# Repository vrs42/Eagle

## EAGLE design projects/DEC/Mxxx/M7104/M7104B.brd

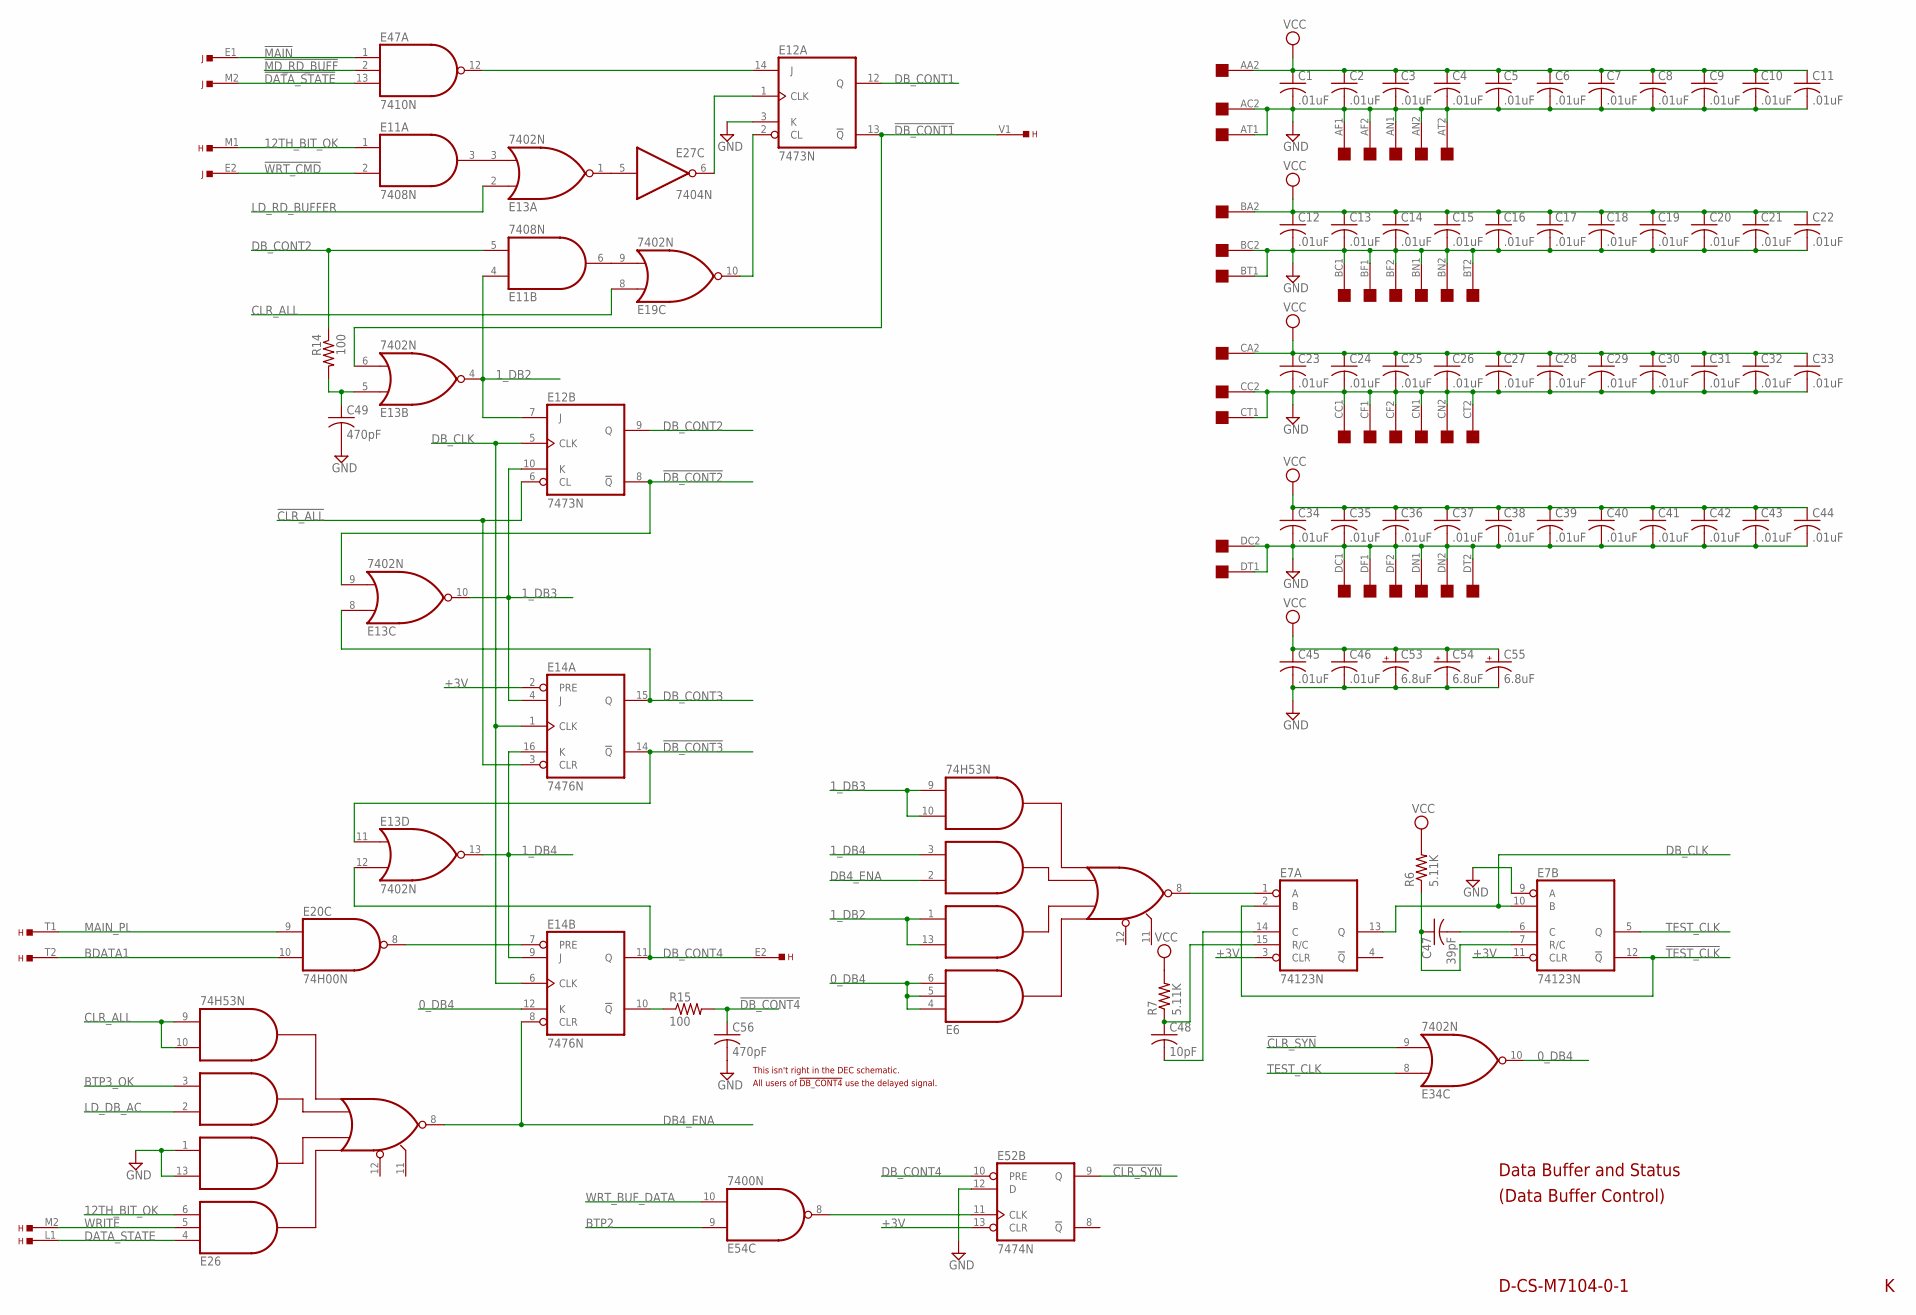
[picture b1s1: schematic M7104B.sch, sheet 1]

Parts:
C1, C2, C3, C4, C5, C6, C7, C8, C9, C10, C11, C12, C13, C14, C15, C16, C17, C18, C19, C20, C21, C22, C23, C24, C25, C26, C27, C28, C29, C30, C31, C32, C33, C34, C35, C36, C37, C38, C39, C40, C41, C42, C43, C44, C45, C46: .01uF; C063-025X075
C47: 39pF; C063-025X075
C48: 10pF; C063-025X075
C49, C56: 470pF; C063-025X075
C53, C54, C55: 6.8uF; E12-8
E6, E26: 74H53N; DIL14
E7: 74123N; DIL16
E11: 7408N; DIL14
E12: 7473N; DIL14
E13, E19, E34: 7402N; DIL14
E14: 7476N; DIL16
E20: 74H00N; DIL14
E27: 7404N; DIL14
E47: 7410N; DIL14
E52: 7474N; DIL14
E54: 7400N; DIL14
H: EDGE-TOP; EDGE-CON2
J: EDGE-TOP; EDGE-CON2
OMNIBUS: QUAD; EDGE-CON8
R6, R7: 5.11K; 0207/15
R14, R15: 100; 0207/10

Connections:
0_DB4: E6.4 (I1), E6.5 (I11), E6.6 (I2), E14.12 (K), E34.10 (O)
1_DB2: E6.1 (I4), E6.13 (I3), E11.4 (I0), E12.7 (J), E13.4 (O)
1_DB3: E6.9 (I8), E6.10 (I7), E12.10 (K), E13.10 (O), E14.4 (J)
1_DB4: E6.3 (I6), E13.13 (O), E14.9 (J), E14.16 (K); also elsewhere on the board
12TH_BIT_OK: E11.1 (I0), E26.6 (I2), H.M1
!CLR_ALL: E12.6 (CL), E14.3 (CLR); also elsewhere on the board
!CLR_SYN: E34.9 (I1), E52.9 (Q)
!DATA_STATE: E47.13 (I2), J.M2
!DB_CONT1: E12.13 (!Q), E13.6 (I1), H.V1
!DB_CONT2: E12.8 (!Q), E13.9 (I1); also elsewhere on the board
!DB_CONT3: E13.11 (I0), E14.14 (!Q)
!DB_CONT4: C56.1, R15.2; also elsewhere on the board
!MAIN: E47.1 (I0), J.E1; also elsewhere on the board
!MD_RD_BUFF: E47.2 (I1); also elsewhere on the board
!TEST_CLK: E7.2 (B), E7.12 (!Q)
!WRT_CMD: E11.2 (I1), J.E2; also elsewhere on the board
+3V: E7.3 (CLR), E7.11 (CLR), E14.2 (PRE), E52.13 (CLR); also elsewhere on the board
BDATA1: E20.10 (I1), H.T2
BTP2: E54.9 (I0); also elsewhere on the board
BTP3_OK: E26.3 (I6); also elsewhere on the board
CLR_ALL: E19.8 (I0), E26.9 (I8), E26.10 (I7); also elsewhere on the board
DATA_STATE: E26.4 (I1), H.L1
DB4_ENA: E6.2 (I5), E14.8 (CLR), E26.8 (O)
DB_CLK: E7.10 (B), E7.13 (Q), E12.5 (CLK), E14.1 (CLK), E14.6 (CLK); also elsewhere on the board
DB_CONT1: E12.12 (Q); also elsewhere on the board
DB_CONT2: E11.5 (I1), E12.9 (Q), R14.1; also elsewhere on the board
DB_CONT3: E13.8 (I0), E14.15 (Q); also elsewhere on the board
DB_CONT4: E13.12 (I1), E14.11 (Q), E52.10 (PRE), H.E2
GND: C1.2, C2.2, C3.2, C4.2, C5.2, C6.2, C7.2, C8.2, C9.2, C10.2, C11.2, C12.2, C13.2, C14.2, C15.2, C16.2, C17.2, C18.2, C19.2, C20.2, C21.2, C22.2, C23.2, C24.2, C25.2, C26.2, C27.2, C28.2, C29.2, C30.2, C31.2, C32.2, C33.2, C34.2, C35.2, C36.2, C37.2, C38.2, C39.2, C40.2, C41.2, C42.2, C43.2, C44.2, C45.2, C46.2, C49.2, C53.-, C54.-, C55.-, C56.2, E6.7 (GND), E7.8 (GND), E7.9 (A), E11.7 (GND), E12.3 (K), E12.11 (GND), E13.7 (GND), E14.13 (GND), E19.7 (GND), E20.7 (GND), E26.1 (I4), E26.7 (GND), E26.13 (I3), E27.7 (GND), E34.7 (GND), E47.7 (GND), E52.7 (GND), E52.12 (D), E54.7 (GND), OMNIBUS.AC2, OMNIBUS.AF1, OMNIBUS.AF2, OMNIBUS.AN1, OMNIBUS.AN2, OMNIBUS.AT1, OMNIBUS.AT2, OMNIBUS.BC1, OMNIBUS.BC2, OMNIBUS.BF1, OMNIBUS.BF2, OMNIBUS.BN1, OMNIBUS.BN2, OMNIBUS.BT1, OMNIBUS.BT2, OMNIBUS.CC1, OMNIBUS.CC2, OMNIBUS.CF1, OMNIBUS.CF2, OMNIBUS.CN1, OMNIBUS.CN2, OMNIBUS.CT1, OMNIBUS.CT2, OMNIBUS.DC1, OMNIBUS.DC2, OMNIBUS.DF1, OMNIBUS.DF2, OMNIBUS.DN1, OMNIBUS.DN2, OMNIBUS.DT1, OMNIBUS.DT2; also elsewhere on the board
LD_DB_AC: E26.2 (I5); also elsewhere on the board
LD_RD_BUFFER: E13.2 (I0); also elsewhere on the board
MAIN_PL: E20.9 (I0), H.T1
unnamed: E14.10 (!Q), R15.1
unnamed: E12.14 (J), E47.12 (O)
unnamed: C48.1, E7.15 (R/C), R7.1
unnamed: E11.3 (O), E13.3 (I1)
unnamed: E13.1 (O), E27.5 (I)
unnamed: E12.1 (CLK), E27.6 (O)
unnamed: E11.6 (O), E19.9 (I1)
unnamed: E12.2 (CL), E19.10 (O)
unnamed: E52.11 (CLK), E54.8 (O)
unnamed: C49.1, E13.5 (I0), R14.2
unnamed: E6.8 (O), E7.1 (A)
unnamed: C47.1, E7.7 (R/C), R6.1
unnamed: C47.2, E7.6 (C)
unnamed: C48.2, E7.14 (C)
unnamed: E14.7 (PRE), E20.8 (O)
TEST_CLK: E7.5 (Q), E34.8 (I0)
VCC: C1.1, C2.1, C3.1, C4.1, C5.1, C6.1, C7.1, C8.1, C9.1, C10.1, C11.1, C12.1, C13.1, C14.1, C15.1, C16.1, C17.1, C18.1, C19.1, C20.1, C21.1, C22.1, C23.1, C24.1, C25.1, C26.1, C27.1, C28.1, C29.1, C30.1, C31.1, C32.1, C33.1, C34.1, C35.1, C36.1, C37.1, C38.1, C39.1, C40.1, C41.1, C42.1, C43.1, C44.1, C45.1, C46.1, C53.+, C54.+, C55.+, E6.14 (VCC), E7.16 (VCC), E11.14 (VCC), E12.4 (VCC), E13.14 (VCC), E14.5 (VCC), E19.14 (VCC), E20.14 (VCC), E26.14 (VCC), E27.14 (VCC), E34.14 (VCC), E47.14 (VCC), E52.14 (VCC), E54.14 (VCC), OMNIBUS.AA2, OMNIBUS.BA2, OMNIBUS.CA2, R6.2, R7.2; also elsewhere on the board
WRITE: E26.5 (I11), H.M2
WRT_BUF_DATA: E54.10 (I1); also elsewhere on the board

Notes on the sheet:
Data Buffer and Status
D-CS-M7104-0-1
(Data Buffer Control)
This isn't right in the DEC schematic.
All users of !DB_CONT4! use the delayed signal.

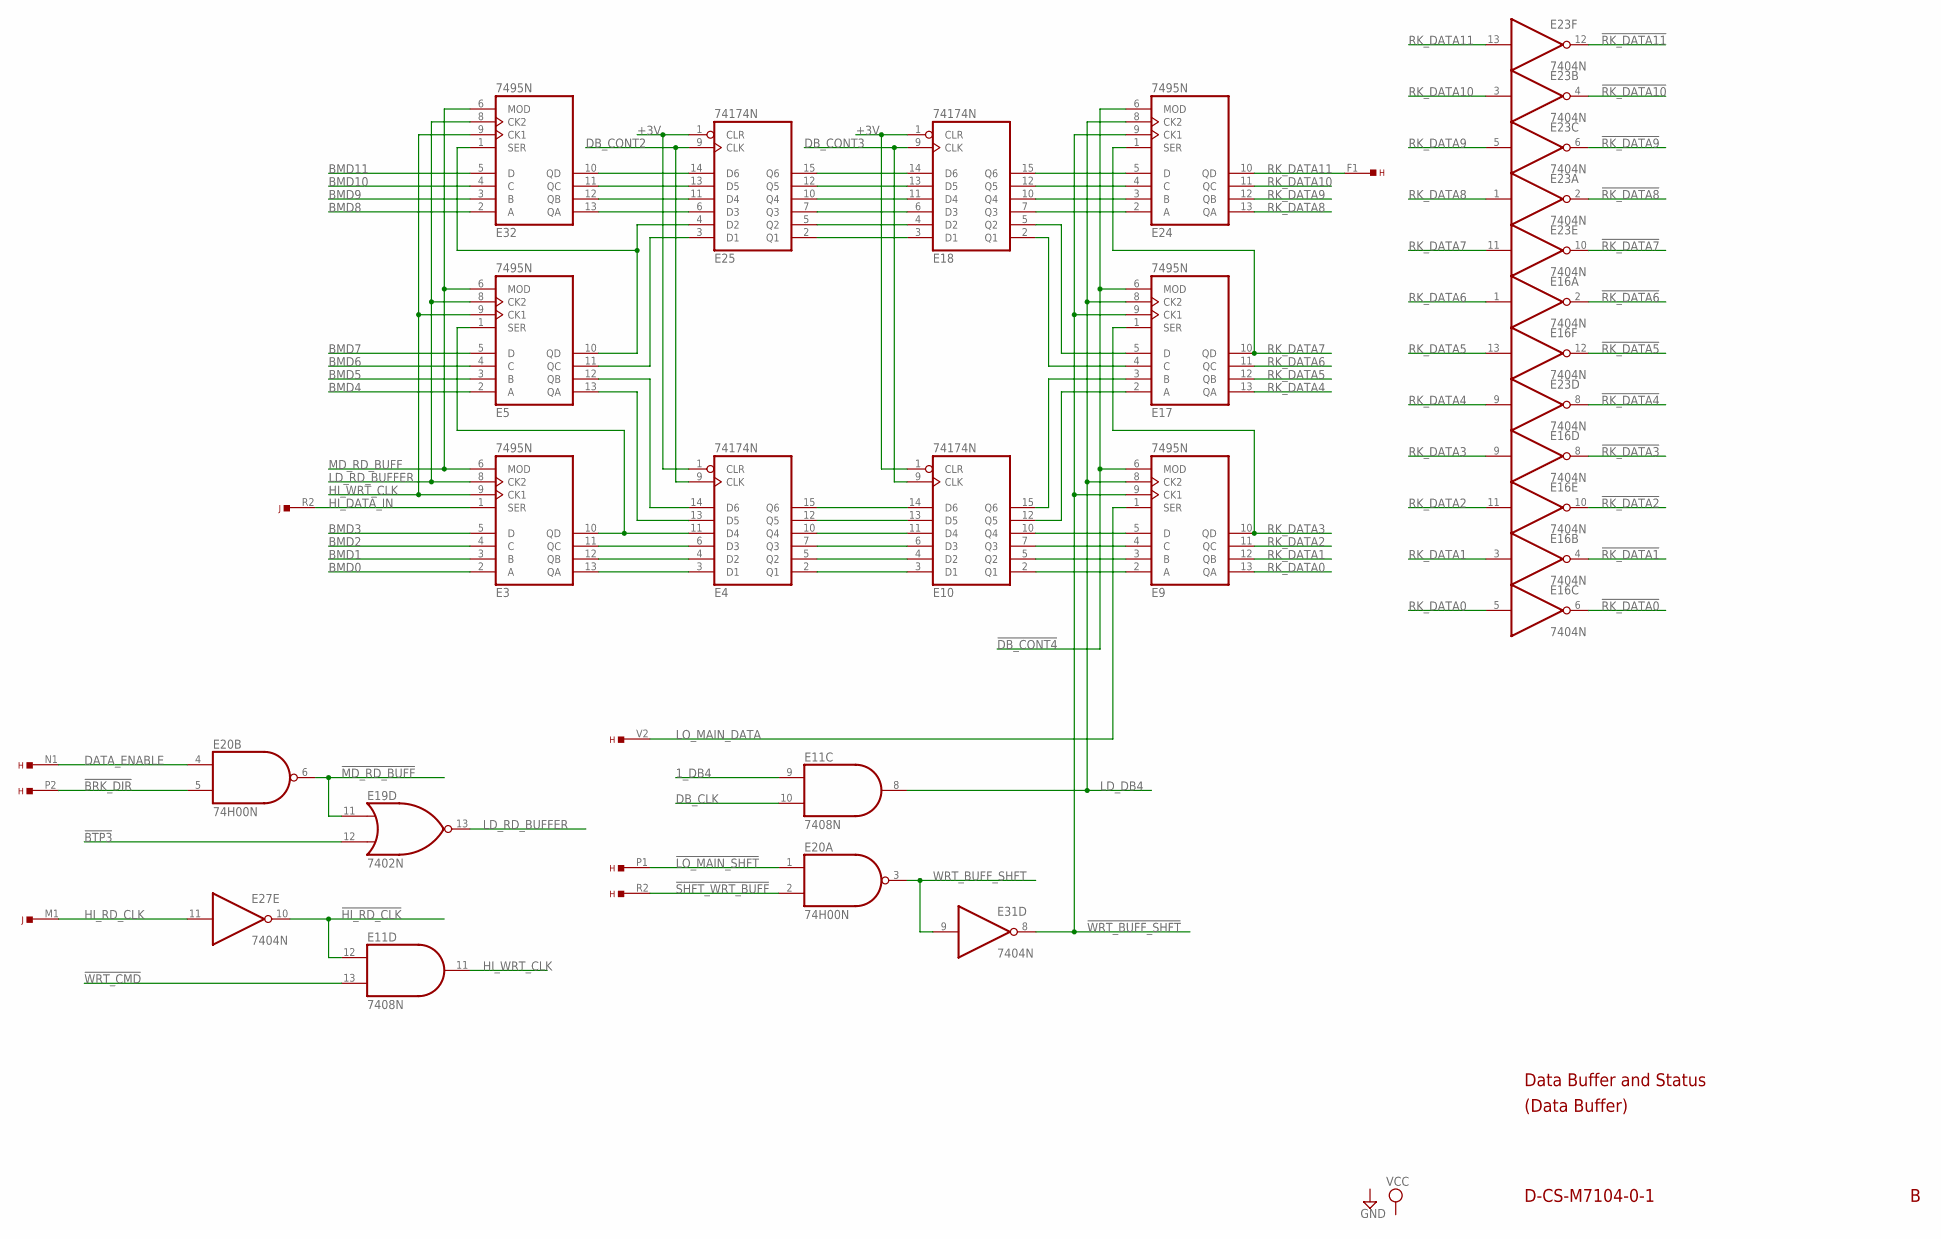
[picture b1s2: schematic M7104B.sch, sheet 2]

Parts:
E3, E5, E9, E17, E24, E32: 7495N; DIL14
E4, E10, E18, E25: 74174N; DIL16
E11: 7408N; DIL14
E16, E23, E27, E31: 7404N; DIL14
E19: 7402N; DIL14
E20: 74H00N; DIL14
H: EDGE-TOP; EDGE-CON2
J: EDGE-TOP; EDGE-CON2

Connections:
1_DB4: E11.9 (I0); also elsewhere on the board
!BRK_DIR: E20.5 (I1), H.P2
!BTP3: E19.12 (I1); also elsewhere on the board
!DB_CONT4: E9.6 (MOD), E17.6 (MOD), E24.6 (MOD); also elsewhere on the board
!HI_RD_CLK: E11.12 (I0), E27.10 (O)
!LO_MAIN_SHFT: E20.1 (I0), H.P1
!MD_RD_BUFF: E19.11 (I0), E20.6 (O); also elsewhere on the board
!RK_DATA0: E16.6 (O); also elsewhere on the board
!RK_DATA1: E16.4 (O); also elsewhere on the board
!RK_DATA2: E16.10 (O); also elsewhere on the board
!RK_DATA3: E16.8 (O); also elsewhere on the board
!RK_DATA4: E23.8 (O); also elsewhere on the board
!RK_DATA5: E16.12 (O); also elsewhere on the board
!RK_DATA6: E16.2 (O); also elsewhere on the board
!RK_DATA7: E23.10 (O); also elsewhere on the board
!RK_DATA8: E23.2 (O); also elsewhere on the board
!RK_DATA9: E23.6 (O); also elsewhere on the board
!RK_DATA10: E23.4 (O); also elsewhere on the board
!RK_DATA11: E23.12 (O); also elsewhere on the board
!SHFT_WRT_BUFF: E20.2 (I1), H.R2
!WRT_BUFF_SHFT: E9.9 (CK1), E17.9 (CK1), E24.9 (CK1), E31.8 (O)
!WRT_CMD: E11.13 (I1); also elsewhere on the board
+3V: E4.1 (CLR), E10.1 (CLR), E18.1 (CLR), E25.1 (CLR); also elsewhere on the board
BMD0: E3.2 (A); also elsewhere on the board
BMD1: E3.3 (B); also elsewhere on the board
BMD2: E3.4 (C); also elsewhere on the board
BMD3: E3.5 (D); also elsewhere on the board
BMD4: E5.2 (A); also elsewhere on the board
BMD5: E5.3 (B); also elsewhere on the board
BMD6: E5.4 (C); also elsewhere on the board
BMD7: E5.5 (D); also elsewhere on the board
BMD8: E32.2 (A); also elsewhere on the board
BMD9: E32.3 (B); also elsewhere on the board
BMD10: E32.4 (C); also elsewhere on the board
BMD11: E32.5 (D); also elsewhere on the board
DATA_ENABLE: E20.4 (I0), H.N1
DB_CLK: E11.10 (I1); also elsewhere on the board
DB_CONT2: E4.9 (CLK), E25.9 (CLK); also elsewhere on the board
DB_CONT3: E10.9 (CLK), E18.9 (CLK); also elsewhere on the board
GND: E3.7 (GND), E4.8 (GND), E5.7 (GND), E9.7 (GND), E10.8 (GND), E11.7 (GND), E16.7 (GND), E17.7 (GND), E18.8 (GND), E19.7 (GND), E20.7 (GND), E23.7 (GND), E24.7 (GND), E25.8 (GND), E27.7 (GND), E31.7 (GND), E32.7 (GND); also elsewhere on the board
HI_DATA_IN: E3.1 (SER), J.R2
HI_RD_CLK: E27.11 (I), J.M1; also elsewhere on the board
HI_WRT_CLK: E3.9 (CK1), E5.9 (CK1), E11.11 (O), E32.9 (CK1)
LD_DB4: E9.8 (CK2), E11.8 (O), E17.8 (CK2), E24.8 (CK2)
LD_RD_BUFFER: E3.8 (CK2), E5.8 (CK2), E19.13 (O), E32.8 (CK2); also elsewhere on the board
LO_MAIN_DATA: E9.1 (SER), H.V2
MD_RD_BUFF: E3.6 (MOD), E5.6 (MOD), E32.6 (MOD); also elsewhere on the board
unnamed: E3.13 (QA), E4.3 (D1)
unnamed: E3.12 (QB), E4.4 (D2)
unnamed: E3.11 (QC), E4.6 (D3)
unnamed: E3.10 (QD), E4.11 (D4), E5.1 (SER)
unnamed: E25.13 (D5), E32.11 (QC)
unnamed: E25.11 (D4), E32.12 (QB)
unnamed: E25.6 (D3), E32.13 (QA)
unnamed: E17.4 (C), E18.2 (Q1)
unnamed: E5.11 (QC), E25.3 (D1)
unnamed: E5.10 (QD), E25.4 (D2), E32.1 (SER)
unnamed: E17.5 (D), E18.5 (Q2)
unnamed: E10.15 (Q6), E17.3 (B)
unnamed: E18.7 (Q3), E24.2 (A)
unnamed: E4.2 (Q1), E10.3 (D1)
unnamed: E4.5 (Q2), E10.4 (D2)
unnamed: E4.7 (Q3), E10.6 (D3)
unnamed: E4.10 (Q4), E10.11 (D4)
unnamed: E4.12 (Q5), E10.13 (D5)
unnamed: E4.15 (Q6), E10.14 (D6)
unnamed: E18.3 (D1), E25.2 (Q1)
unnamed: E18.4 (D2), E25.5 (Q2)
unnamed: E18.6 (D3), E25.7 (Q3)
unnamed: E18.11 (D4), E25.10 (Q4)
unnamed: E18.13 (D5), E25.12 (Q5)
unnamed: E18.14 (D6), E25.15 (Q6)
unnamed: E18.10 (Q4), E24.3 (B)
unnamed: E18.12 (Q5), E24.4 (C)
unnamed: E18.15 (Q6), E24.5 (D)
unnamed: E10.12 (Q5), E17.2 (A)
unnamed: E9.5 (D), E10.10 (Q4)
unnamed: E4.14 (D6), E5.12 (QB)
unnamed: E4.13 (D5), E5.13 (QA)
unnamed: E25.14 (D6), E32.10 (QD)
unnamed: E9.4 (C), E10.7 (Q3)
unnamed: E9.3 (B), E10.5 (Q2)
unnamed: E9.2 (A), E10.2 (Q1)
RK_DATA0: E9.13 (QA), E16.5 (I)
RK_DATA1: E9.12 (QB), E16.3 (I)
RK_DATA2: E9.11 (QC), E16.11 (I)
RK_DATA3: E9.10 (QD), E16.9 (I), E17.1 (SER)
RK_DATA4: E17.13 (QA), E23.9 (I)
RK_DATA5: E16.13 (I), E17.12 (QB)
RK_DATA6: E16.1 (I), E17.11 (QC)
RK_DATA7: E17.10 (QD), E23.11 (I), E24.1 (SER)
RK_DATA8: E23.1 (I), E24.13 (QA)
RK_DATA9: E23.5 (I), E24.12 (QB)
RK_DATA10: E23.3 (I), E24.11 (QC)
RK_DATA11: E23.13 (I), E24.10 (QD), H.F1
VCC: E3.14 (VCC), E4.16 (VCC), E5.14 (VCC), E9.14 (VCC), E10.16 (VCC), E11.14 (VCC), E16.14 (VCC), E17.14 (VCC), E18.16 (VCC), E19.14 (VCC), E20.14 (VCC), E23.14 (VCC), E24.14 (VCC), E25.16 (VCC), E27.14 (VCC), E31.14 (VCC), E32.14 (VCC); also elsewhere on the board
WRT_BUFF_SHFT: E20.3 (O), E31.9 (I)

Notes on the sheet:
Data Buffer and Status
D-CS-M7104-0-1
(Data Buffer)

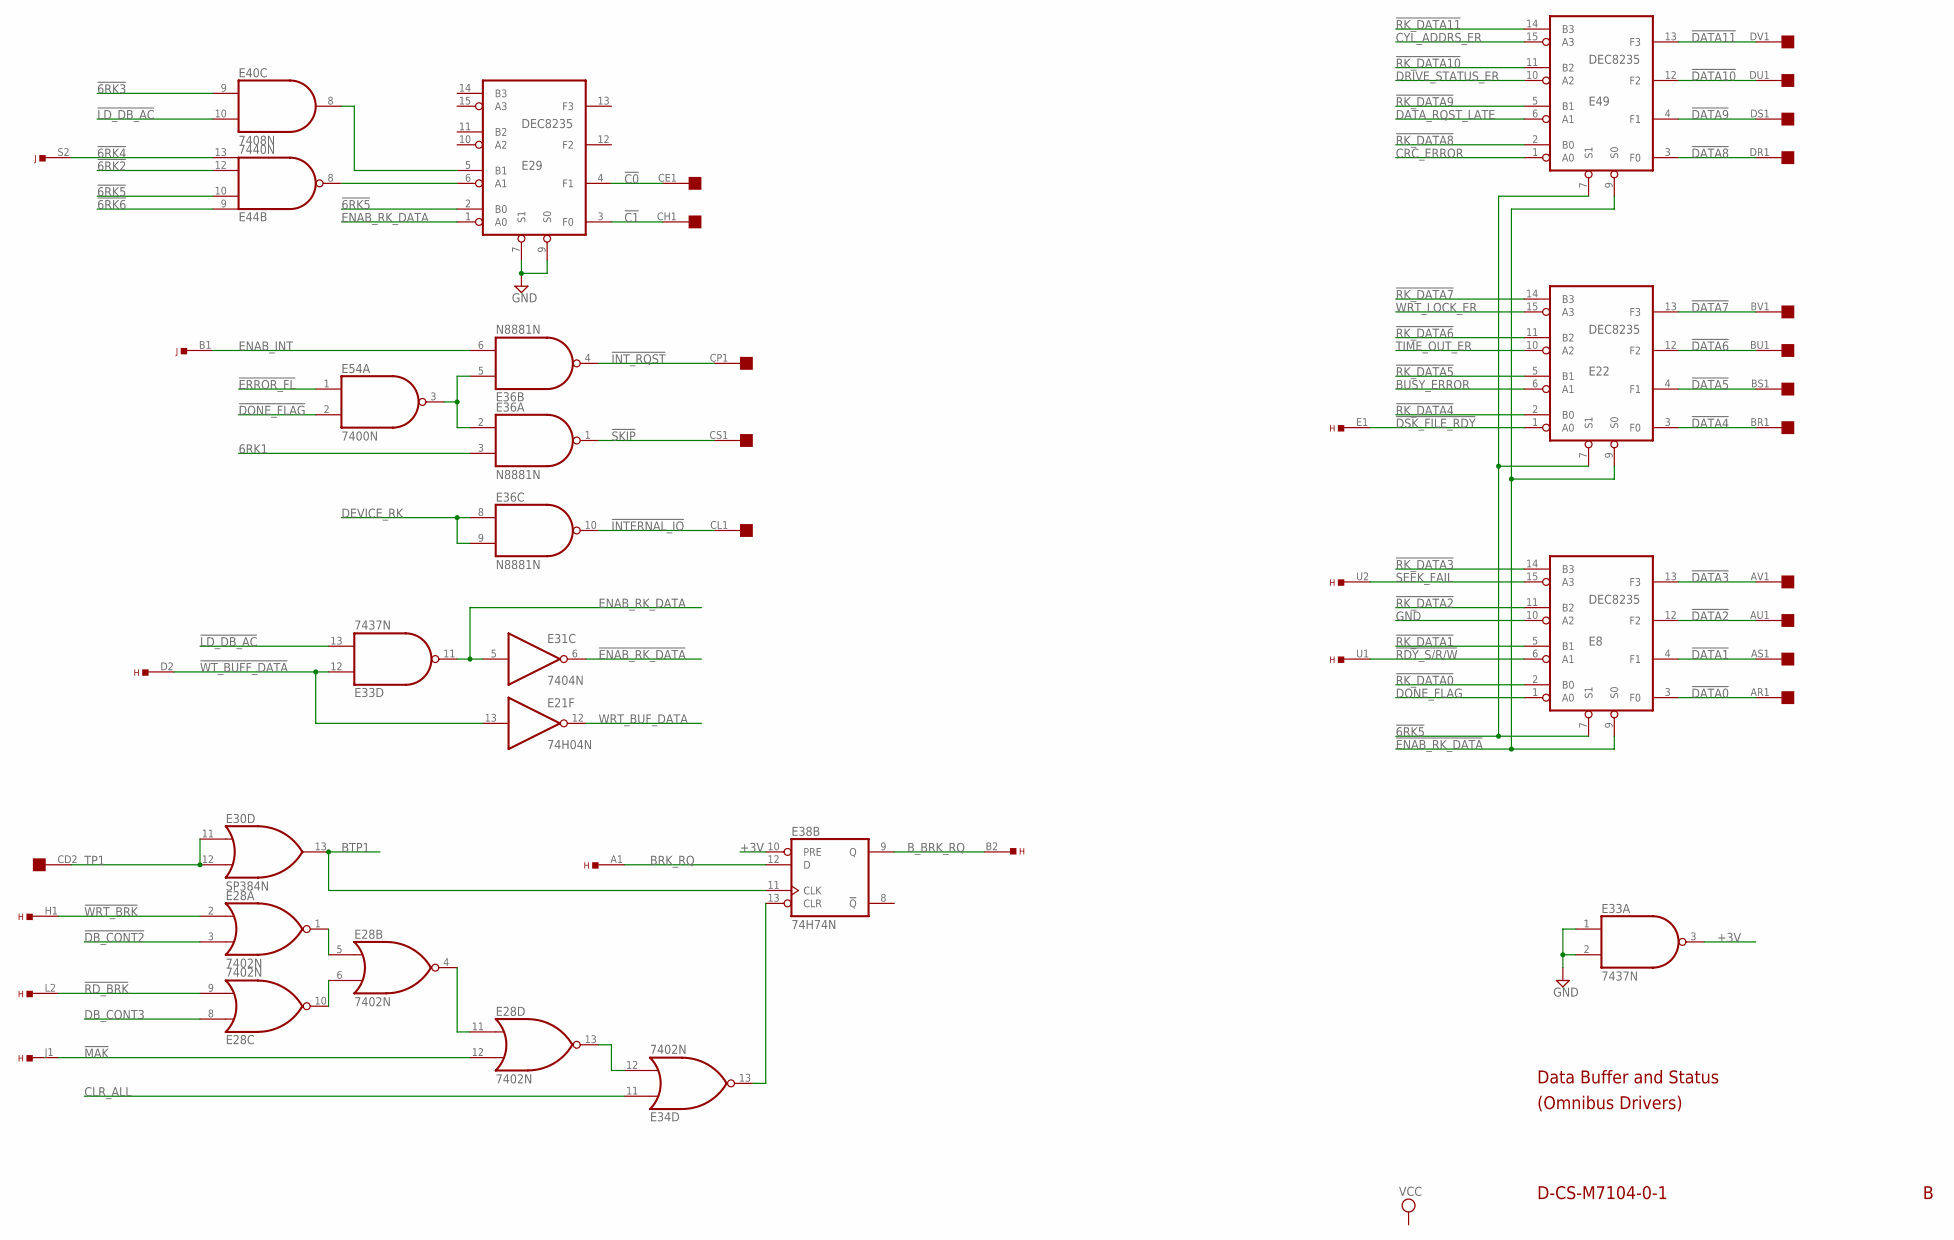
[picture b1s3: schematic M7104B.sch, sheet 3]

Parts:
E8, E22, E29, E49: DEC8235; DIL16
E21: 74H04N; DIL14
E28, E34: 7402N; DIL14
E30: SP384N; DIL14
E31: 7404N; DIL14
E33: 7437N; DIL14
E36: N8881N; DIL14
E38: 74H74N; DIL14
E40: 7408N; DIL14
E44: 7440N; DIL14
E54: 7400N; DIL14
H: EDGE-TOP; EDGE-CON2
J: EDGE-TOP; EDGE-CON2
OMNIBUS: QUAD; EDGE-CON8

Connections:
6RK1: E36.3 (I1); also elsewhere on the board
!6RK2: E44.12 (I2); also elsewhere on the board
!6RK3: E40.9 (I0); also elsewhere on the board
!6RK4: E44.13 (I3), J.S2; also elsewhere on the board
!6RK5: E8.7 (S1), E22.7 (S1), E29.2 (B0), E44.10 (I1), E49.7 (S1); also elsewhere on the board
!6RK6: E44.9 (I0); also elsewhere on the board
!C0: E29.4 (F1), OMNIBUS.CE1
!C1: E29.3 (F0), OMNIBUS.CH1
!DATA0: E8.3 (F0), OMNIBUS.AR1
!DATA1: E8.4 (F1), OMNIBUS.AS1
!DATA2: E8.12 (F2), OMNIBUS.AU1
!DATA3: E8.13 (F3), OMNIBUS.AV1
!DATA4: E22.3 (F0), OMNIBUS.BR1
!DATA5: E22.4 (F1), OMNIBUS.BS1
!DATA6: E22.12 (F2), OMNIBUS.BU1
!DATA7: E22.13 (F3), OMNIBUS.BV1; also elsewhere on the board
!DATA8: E49.3 (F0), OMNIBUS.DR1
!DATA9: E49.4 (F1), OMNIBUS.DS1
!DATA10: E49.12 (F2), OMNIBUS.DU1
!DATA11: E49.13 (F3), OMNIBUS.DV1
!DB_CONT2: E28.3 (I1); also elsewhere on the board
!DONE_FLAG: E54.2 (I1); also elsewhere on the board
!DSK_FILE_RDY: E22.1 (A0), H.E1
!ENAB_RK_DATA: E8.9 (S0), E22.9 (S0), E31.6 (O), E49.9 (S0)
!ERROR_FL: E54.1 (I0); also elsewhere on the board
!INTERNAL_IO: E36.10 (O), OMNIBUS.CL1
!INT_RQST: E36.4 (O), OMNIBUS.CP1
!LD_DB_AC: E33.13 (I1), E40.10 (I1); also elsewhere on the board
!MAK: E28.12 (I1), H.J1
!RDY_S/R/W: E8.6 (A1), H.U1
!RD_BRK: E28.9 (I1), H.L2
!RK_DATA0: E8.2 (B0); also elsewhere on the board
!RK_DATA1: E8.5 (B1); also elsewhere on the board
!RK_DATA2: E8.11 (B2); also elsewhere on the board
!RK_DATA3: E8.14 (B3); also elsewhere on the board
!RK_DATA4: E22.2 (B0); also elsewhere on the board
!RK_DATA5: E22.5 (B1); also elsewhere on the board
!RK_DATA6: E22.11 (B2); also elsewhere on the board
!RK_DATA7: E22.14 (B3); also elsewhere on the board
!RK_DATA8: E49.2 (B0); also elsewhere on the board
!RK_DATA9: E49.5 (B1); also elsewhere on the board
!RK_DATA10: E49.11 (B2); also elsewhere on the board
!RK_DATA11: E49.14 (B3); also elsewhere on the board
!SKIP: E36.1 (O), OMNIBUS.CS1
!WRT_BRK: E28.2 (I0), H.H1
!WT_BUFF_DATA: E21.13 (I), E33.12 (I0), H.D2
+3V: E33.3 (O), E38.10 (PRE); also elsewhere on the board
BRK_RQ: E38.12 (D), H.A1
BTP1: E30.13 (O), E38.11 (CLK)
BUSY_ERROR: E22.6 (A1); also elsewhere on the board
B_BRK_RQ: E38.9 (Q), H.B2
CLR_ALL: E34.11 (I0); also elsewhere on the board
CRC_ERROR: E49.1 (A0); also elsewhere on the board
CYL_ADDRS_ER: E49.15 (A3); also elsewhere on the board
DATA_RQST_LATE: E49.6 (A1); also elsewhere on the board
DB_CONT3: E28.8 (I0); also elsewhere on the board
DEVICE_RK: E36.8 (I0), E36.9 (I1); also elsewhere on the board
DONE_FLAG: E8.1 (A0); also elsewhere on the board
DRIVE_STATUS_ER: E49.10 (A2); also elsewhere on the board
ENAB_INT: E36.6 (I1), J.B1
ENAB_RK_DATA: E29.1 (A0), E31.5 (I), E33.11 (O)
GND: E8.8 (GND), E8.10 (A2), E21.7 (GND), E22.8 (GND), E28.7 (GND), E29.7 (S1), E29.8 (GND), E29.9 (S0), E30.1 (GND), E31.7 (GND), E33.1 (I0), E33.2 (I1), E33.7 (GND), E34.7 (GND), E36.7 (GND), E38.7 (GND), E40.7 (GND), E44.7 (GND), E49.8 (GND), E54.7 (GND); also elsewhere on the board
unnamed: E29.6 (A1), E44.8 (O)
unnamed: E29.5 (B1), E40.8 (O)
unnamed: E36.2 (I0), E36.5 (I0), E54.3 (O)
unnamed: E28.1 (O), E28.5 (I0)
unnamed: E28.6 (I1), E28.10 (O)
unnamed: E28.4 (O), E28.11 (I0)
unnamed: E34.13 (O), E38.13 (CLR)
unnamed: E28.13 (O), E34.12 (I1)
SEEK_FAIL: E8.15 (A3), H.U2
TIME_OUT_ER: E22.10 (A2); also elsewhere on the board
TP1: E30.11 (I0), E30.12 (I1), OMNIBUS.CD2
VCC: E8.16 (VCC), E21.14 (VCC), E22.16 (VCC), E28.14 (VCC), E29.16 (VCC), E30.8 (VCC), E31.14 (VCC), E33.14 (VCC), E34.14 (VCC), E36.14 (VCC), E38.14 (VCC), E40.14 (VCC), E44.14 (VCC), E49.16 (VCC), E54.14 (VCC); also elsewhere on the board
WRT_BUF_DATA: E21.12 (O); also elsewhere on the board
WRT_LOCK_ER: E22.15 (A3); also elsewhere on the board

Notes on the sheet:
Data Buffer and Status
D-CS-M7104-0-1
(Omnibus Drivers)

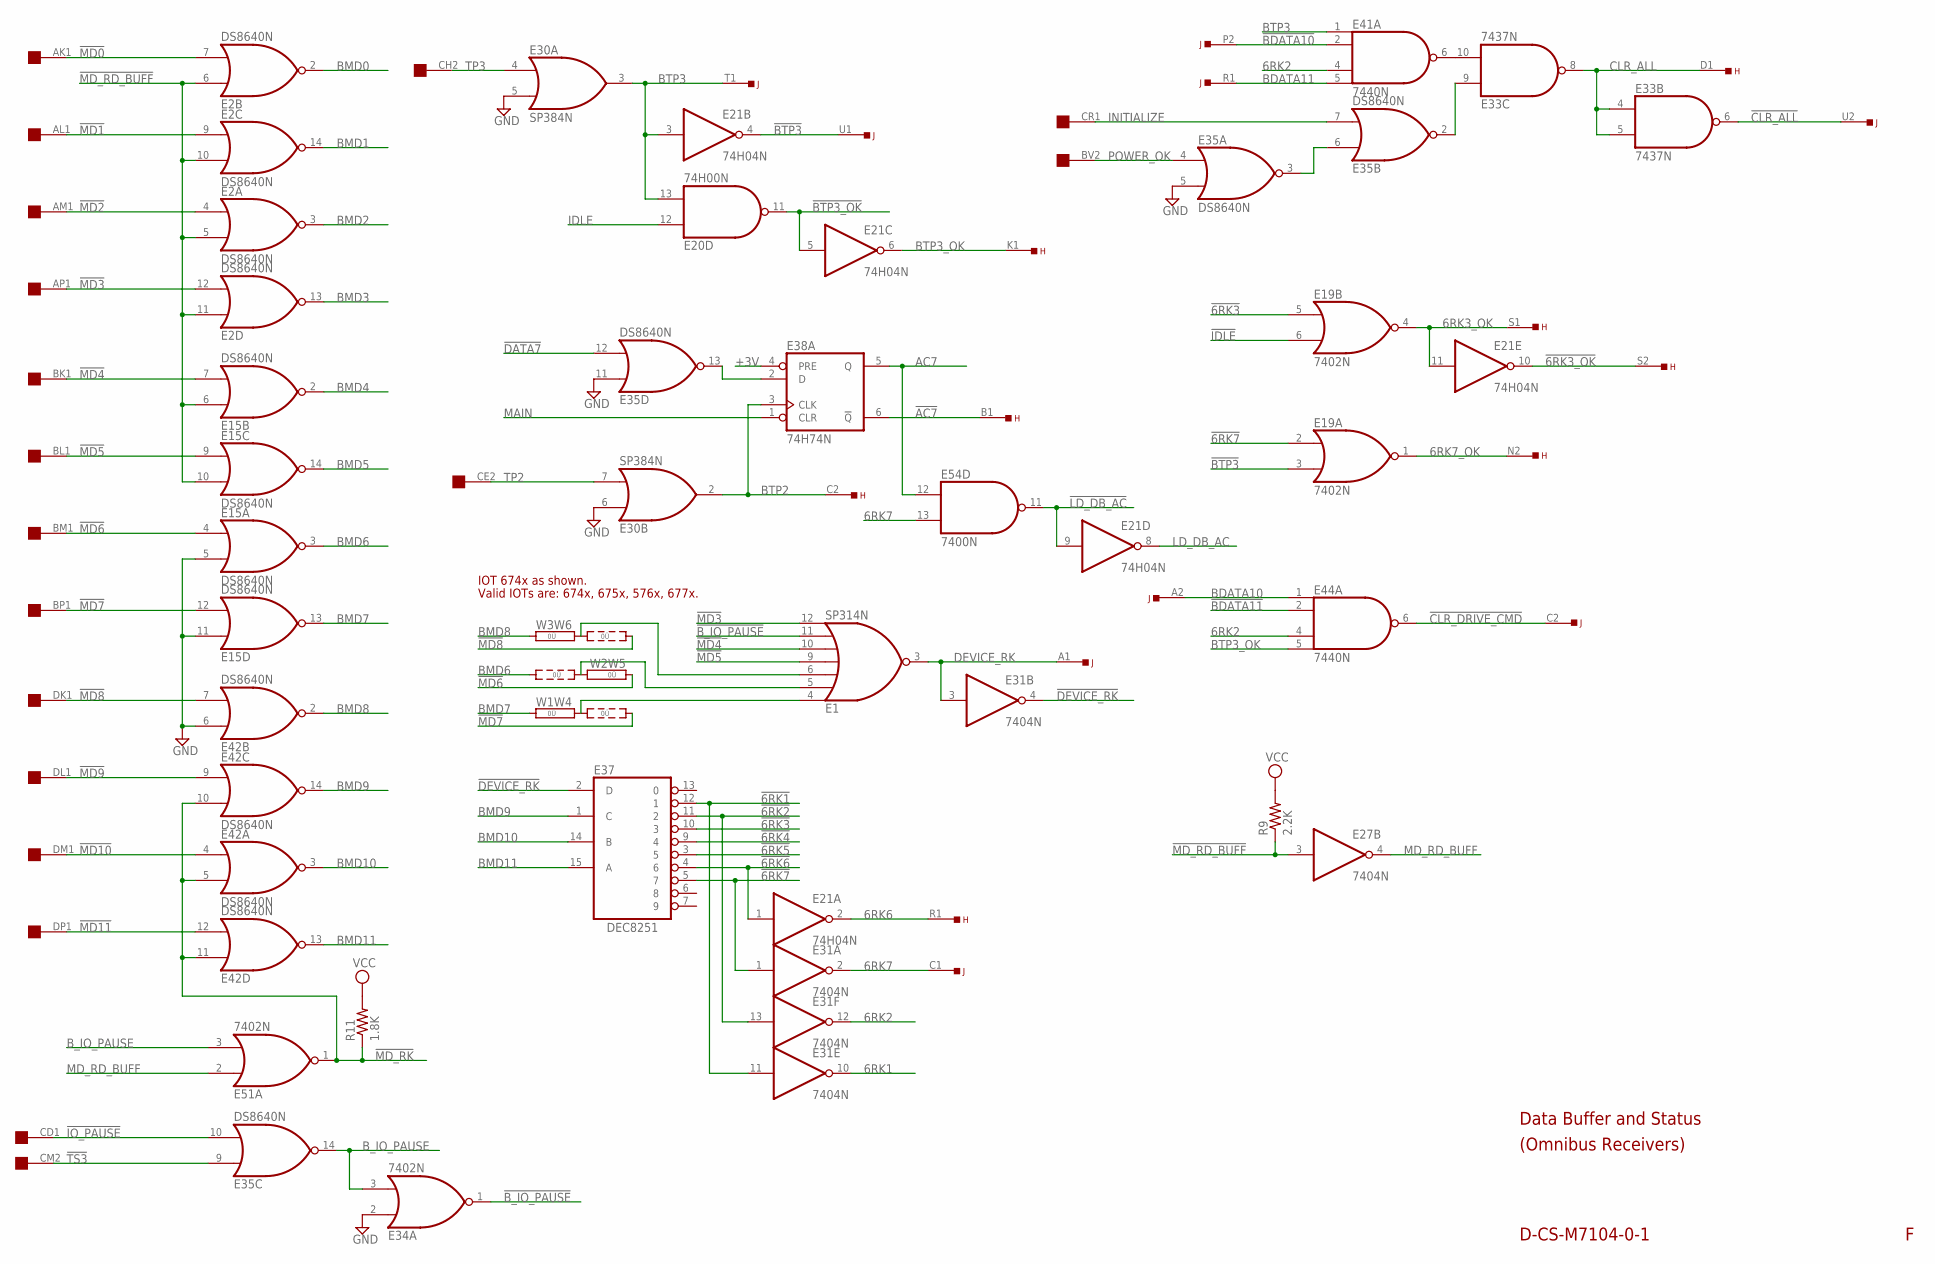
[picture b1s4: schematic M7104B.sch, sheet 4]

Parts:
E1: SP314N; DIL14
E2, E15, E35, E42: DS8640N; DIL14
E19, E34, E51: 7402N; DIL14
E20: 74H00N; DIL14
E21: 74H04N; DIL14
E27, E31: 7404N; DIL14
E30: SP384N; DIL14
E33: 7437N; DIL14
E37: DEC8251; DIL16
E38: 74H74N; DIL14
E41, E44: 7440N; DIL14
E54: 7400N; DIL14
H: EDGE-TOP; EDGE-CON2
J: EDGE-TOP; EDGE-CON2
OMNIBUS: QUAD; EDGE-CON8
R9: 2.2K; 0207/10
R11: 1.8K; 0207/10
W1W4, W2W5, W3W6: 0R2; 0R2/10

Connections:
6RK1: E31.10 (O); also elsewhere on the board
6RK2: E31.12 (O), E41.4 (I2), E44.4 (I2); also elsewhere on the board
6RK3_OK: E19.4 (O), E21.11 (I), H.S1
6RK6: E21.2 (O), H.R1
6RK7: E31.2 (O), E54.13 (I1), J.C1
6RK7_OK: E19.1 (O), H.N2
!6RK1: E31.11 (I), E37.12 (1)
!6RK2: E31.13 (I), E37.11 (2); also elsewhere on the board
!6RK3: E19.5 (I0), E37.10 (3); also elsewhere on the board
!6RK3_OK: E21.10 (O), H.S2
!6RK4: E37.9 (4); also elsewhere on the board
!6RK5: E37.3 (5); also elsewhere on the board
!6RK6: E21.1 (I), E37.4 (6); also elsewhere on the board
!6RK7: E19.2 (I0), E31.1 (I), E37.5 (7)
!AC7: E38.6 (!Q), H.B1
!BDATA10: E41.2 (I1), J.P2
!BDATA11: E44.2 (I1); also elsewhere on the board
!BTP3: E19.3 (I1), E21.4 (O), J.U1; also elsewhere on the board
!BTP3_OK: E20.11 (O), E21.5 (I)
!B_IO_PAUSE: E1.11 (I5), E34.1 (O)
!CLR_ALL: E33.6 (O), J.U2; also elsewhere on the board
!CLR_DRIVE_CMD: E44.6 (O), J.C2; also elsewhere on the board
!DATA7: E35.12 (I1); also elsewhere on the board
!DEVICE_RK: E31.4 (O), E37.2 (D)
!IDLE: E19.6 (I1); also elsewhere on the board
!IO_PAUSE: E35.10 (I1), OMNIBUS.CD1
!LD_DB_AC: E21.9 (I), E54.11 (O); also elsewhere on the board
!MD0: E2.7 (I1), OMNIBUS.AK1
!MD1: E2.9 (I0), OMNIBUS.AL1
!MD2: E2.4 (I0), OMNIBUS.AM1
!MD3: E1.12 (I6), E2.12 (I1), OMNIBUS.AP1
!MD4: E1.10 (I4), E15.7 (I1), OMNIBUS.BK1
!MD5: E1.9 (I3), E15.9 (I0), OMNIBUS.BL1
!MD6: E15.4 (I0), OMNIBUS.BM1, W2W5.1
!MD7: E15.12 (I1), OMNIBUS.BP1, W1W4.3
!MD8: E42.7 (I1), OMNIBUS.DK1, W3W6.3
!MD9: E42.9 (I0), OMNIBUS.DL1
!MD10: E42.4 (I0), OMNIBUS.DM1
!MD11: E42.12 (I1), OMNIBUS.DP1
!MD_RD_BUFF: E2.5 (I1), E2.6 (I0), E2.10 (I1), E2.11 (I0), E15.6 (I0), E15.10 (I1), E27.3 (I), R9.1; also elsewhere on the board
!MD_RK: E42.5 (I1), E42.10 (I1), E42.11 (I0), E51.1 (O), R11.1
!TS3: E35.9 (I0), OMNIBUS.CM2
+3V: E38.4 (PRE); also elsewhere on the board
AC7: E38.5 (Q), E54.12 (I0)
BDATA10: E44.1 (I0), J.A2
BDATA11: E41.5 (I3), J.R1
BMD0: E2.2 (O); also elsewhere on the board
BMD1: E2.14 (O); also elsewhere on the board
BMD2: E2.3 (O); also elsewhere on the board
BMD3: E2.13 (O); also elsewhere on the board
BMD4: E15.2 (O); also elsewhere on the board
BMD5: E15.14 (O); also elsewhere on the board
BMD6: E15.3 (O), W2W5.3; also elsewhere on the board
BMD7: E15.13 (O), W1W4.1; also elsewhere on the board
BMD8: E42.2 (O), W3W6.1; also elsewhere on the board
BMD9: E37.1 (C), E42.14 (O); also elsewhere on the board
BMD10: E37.14 (B), E42.3 (O); also elsewhere on the board
BMD11: E37.15 (A), E42.13 (O); also elsewhere on the board
BTP2: E30.2 (O), E38.3 (CLK), H.C2; also elsewhere on the board
BTP3: E20.13 (I1), E21.3 (I), E30.3 (O), E41.1 (I0), J.T1; also elsewhere on the board
BTP3_OK: E21.6 (O), E44.5 (I3), H.K1; also elsewhere on the board
B_IO_PAUSE: E34.3 (I1), E35.14 (O), E51.3 (I1)
CLR_ALL: E33.4 (I0), E33.5 (I1), E33.8 (O), H.D1; also elsewhere on the board
DEVICE_RK: E1.3 (O), E31.3 (I), J.A1; also elsewhere on the board
GND: E1.1 (GND), E2.1 (GND), E15.1 (GND), E15.5 (I1), E15.11 (I0), E19.7 (GND), E20.7 (GND), E21.7 (GND), E27.7 (GND), E30.1 (GND), E30.5 (I1), E30.6 (I0), E31.7 (GND), E33.7 (GND), E34.2 (I0), E34.7 (GND), E35.1 (GND), E35.5 (I1), E35.11 (I0), E37.8 (GND), E38.7 (GND), E41.7 (GND), E42.1 (GND), E42.6 (I0), E44.7 (GND), E51.7 (GND), E54.7 (GND); also elsewhere on the board
IDLE: E20.12 (I0); also elsewhere on the board
INITIALIZE: E35.7 (I1), OMNIBUS.CR1
LD_DB_AC: E21.8 (O); also elsewhere on the board
MAIN: E38.1 (CLR); also elsewhere on the board
MD_RD_BUFF: E27.4 (O), E51.2 (I0); also elsewhere on the board
unnamed: E35.13 (O), E38.2 (D)
unnamed: E33.10 (I1), E41.6 (O)
unnamed: E1.4 (I0), W1W4.2
unnamed: E1.5 (I1), W2W5.2
unnamed: E1.6 (I2), W3W6.2
unnamed: E35.3 (O), E35.6 (I0)
unnamed: E33.9 (I0), E35.2 (O)
POWER_OK: E35.4 (I0), OMNIBUS.BV2
TP2: E30.7 (I1), OMNIBUS.CE2
TP3: E30.4 (I0), OMNIBUS.CH2
VCC: E1.8 (VCC), E2.8 (VCC), E15.8 (VCC), E19.14 (VCC), E20.14 (VCC), E21.14 (VCC), E27.14 (VCC), E30.8 (VCC), E31.14 (VCC), E33.14 (VCC), E34.14 (VCC), E35.8 (VCC), E37.16 (VCC), E38.14 (VCC), E41.14 (VCC), E42.8 (VCC), E44.14 (VCC), E51.14 (VCC), E54.14 (VCC), R9.2, R11.2; also elsewhere on the board

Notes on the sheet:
Data Buffer and Status
D-CS-M7104-0-1
(Omnibus Receivers)
IOT 674x as shown.
Valid IOTs are: 674x, 675x, 576x, 677x.
